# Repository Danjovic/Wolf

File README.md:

# Wolf - Warning: Beta
Atari Jaguar/SNES controller adapter for emulate a Joystick and a Keypad for systems 2600 and 7800

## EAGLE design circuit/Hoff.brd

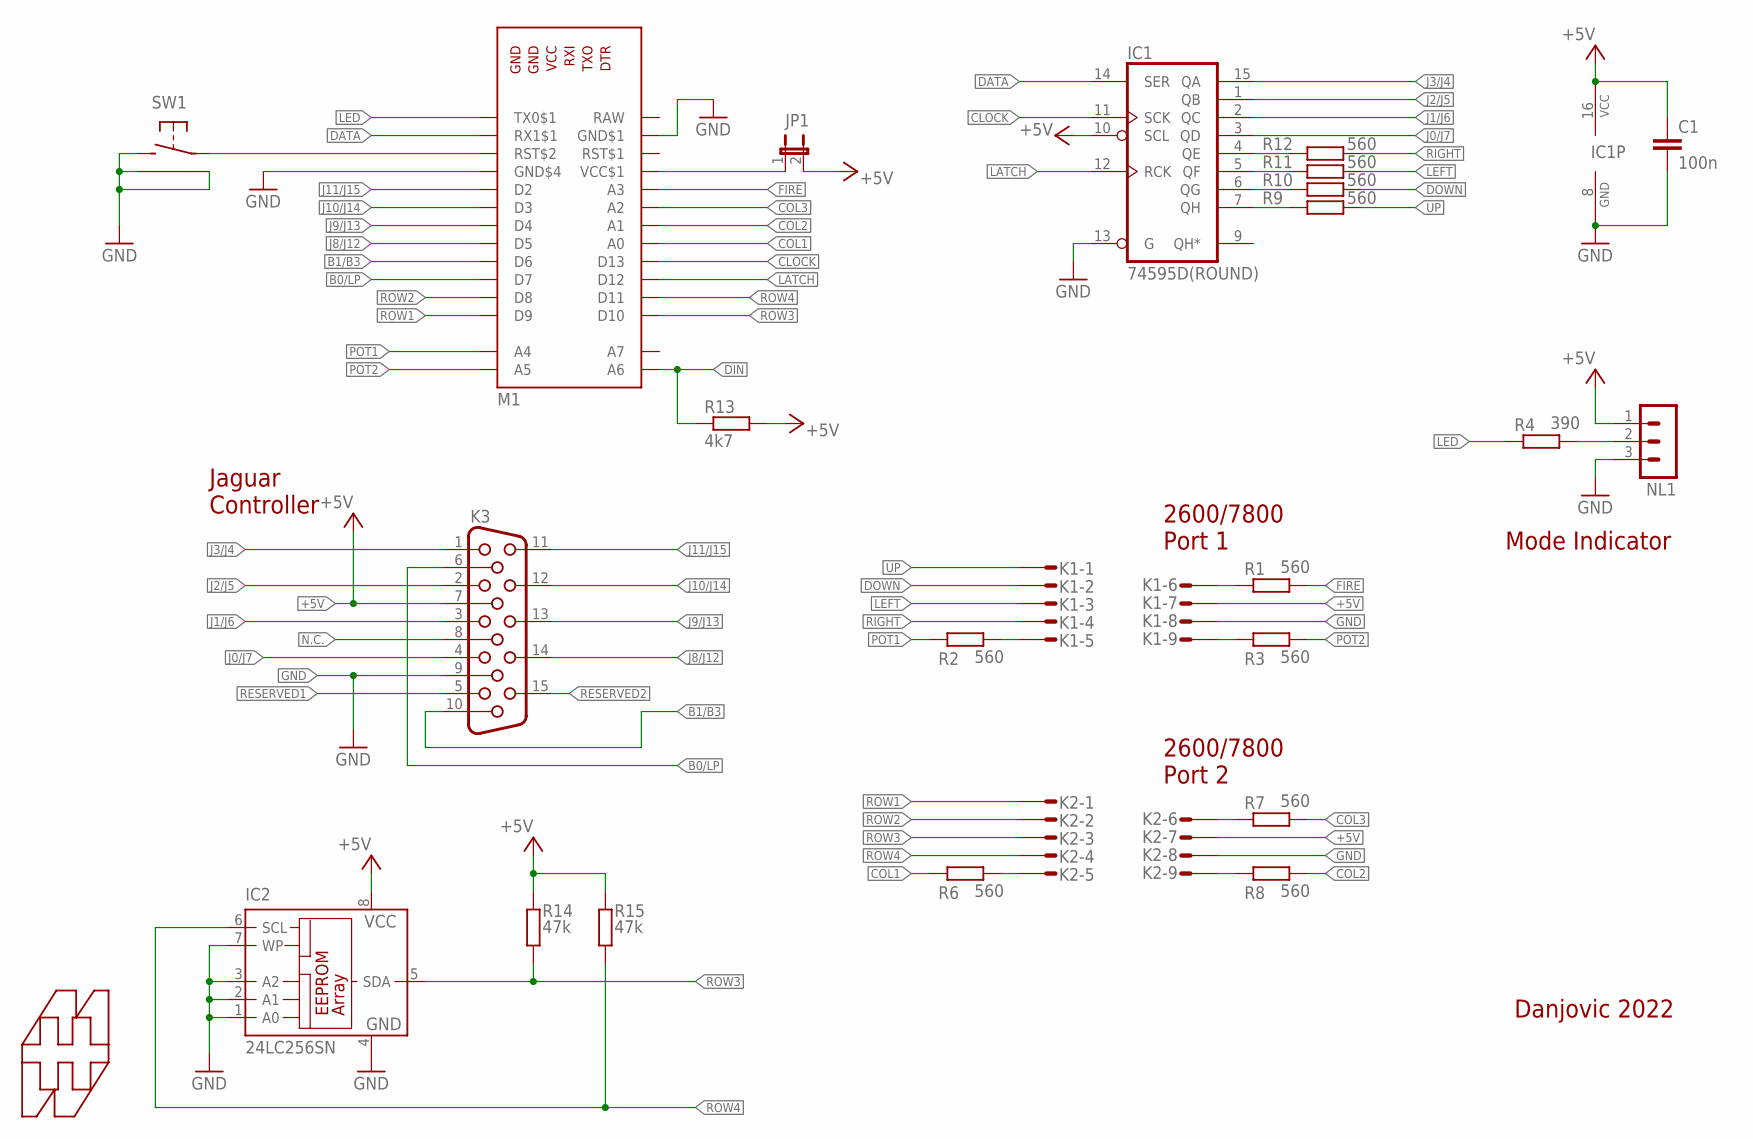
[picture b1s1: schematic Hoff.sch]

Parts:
C1: 100n; C050-024X044
IC1: 74595D(ROUND); DIL16-ROUND
IC2: 24LC256SN; SO-08
JP1: JP1E; JP1
K1, K2: S09P
K3: HF15H; HDF15H
M1: ARDUINO_PRO_MINI_SIDE_ONLY; ARDUNIO_PRO_MINI_SIDE_ONLY
NL1: MA03-1
R1, R2, R3, R6, R7, R8, R9, R10, R11, R12: 560; 0204/7
R4: 390; 0204/7
R13: 4k7; 0204/7
R14, R15: 47k; 0204/7
SW: 31-XX-GG; B3F-31XX
U$1: HAMMOND-1593J; 1593J

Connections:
!RESET: M1.RST$2, SW.1
+5V: C1.1, IC1.10 (SCL), IC1.16 (VCC), IC2.8 (VCC), JP1.2, K1.7, K2.7, K3.7, NL1.1, R13.2, R14.2, R15.2
B0/LP: K3.6, M1.D7
B1/B3: K3.10, M1.D6
CLOCK: IC1.11 (SCK), M1.D13
COL1: M1.A0, R6.1
COL2: M1.A1, R8.2
COL3: M1.A2, R7.2
DATA: IC1.14 (SER), M1.RX1$1
DIN: M1.A6, R13.1
DOWN: K1.2, R10.2
FIRE: M1.A3, R1.2
GND: C1.2, IC1.8 (GND), IC1.13 (G), IC2.1 (A0), IC2.2 (A1), IC2.3 (A2), IC2.4 (GND), IC2.7 (WP), K1.8, K2.8, K3.9, M1.GDN$1 (GND$1), M1.GND$4, NL1.3, SW.2 (S), SW.3, SW.4
J0/J7: IC1.3 (QD), K3.4
J1/J6: IC1.2 (QC), K3.3
J2/J5: IC1.1 (QB), K3.2
J3/J4: IC1.15 (QA), K3.1
J8/J12: K3.14, M1.D5
J9/J13: K3.13, M1.D4
J10/J14: K3.12, M1.D3
J11/J15: K3.11, M1.D2
LATCH: IC1.12 (RCK), M1.D12
LED: M1.TX0$1, R4.1
LEFT: K1.3, R11.2
unnamed: NL1.2, R4.2
unnamed: JP1.1, M1.VCC$1
N.C.: K3.8
POT1: M1.A4, R2.1
POT2: M1.A5, R3.2
RAW: M1.RAW
RESERVED1: K3.5
RESERVED2: K3.15
RIGHT: K1.4, R12.2
ROW1: K2.1, M1.D9
ROW2: K2.2, M1.D8
ROW3: IC2.5 (SDA), K2.3, M1.D10, R14.1
ROW4: IC2.6 (SCL), K2.4, M1.D11, R15.1
R_COL1: K2.5, R6.2
R_COL2: K2.9, R8.1
R_COL3: K2.6, R7.1
R_DOWN: IC1.6 (QG), R10.1
R_FIRE: K1.6, R1.1
R_LEFT: IC1.5 (QF), R11.1
R_POT1: K1.5, R2.2
R_POT2: K1.9, R3.1
R_RIGHT: IC1.4 (QE), R12.1
R_UP: IC1.7 (QH), R9.1
UP: K1.1, R9.2

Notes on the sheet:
Danjovic 2022
Jaguar Controller
2600/7800 Port 1
2600/7800 Port 2
Mode Indicator

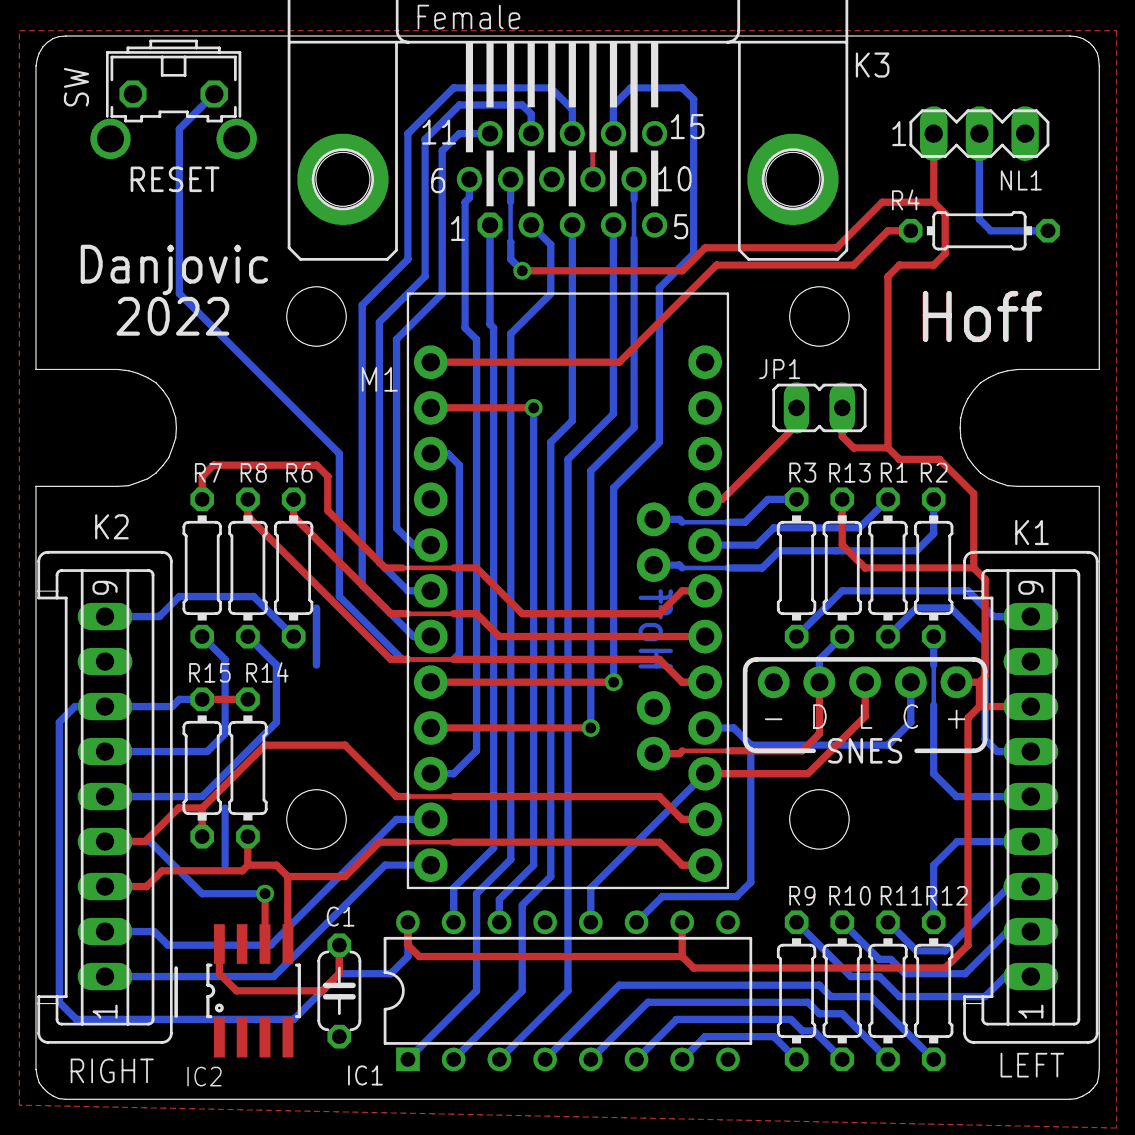
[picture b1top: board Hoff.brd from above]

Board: 2 copper layers, 59.1 x 59.1 mm, 25 parts (0 on the bottom side), 44 nets.

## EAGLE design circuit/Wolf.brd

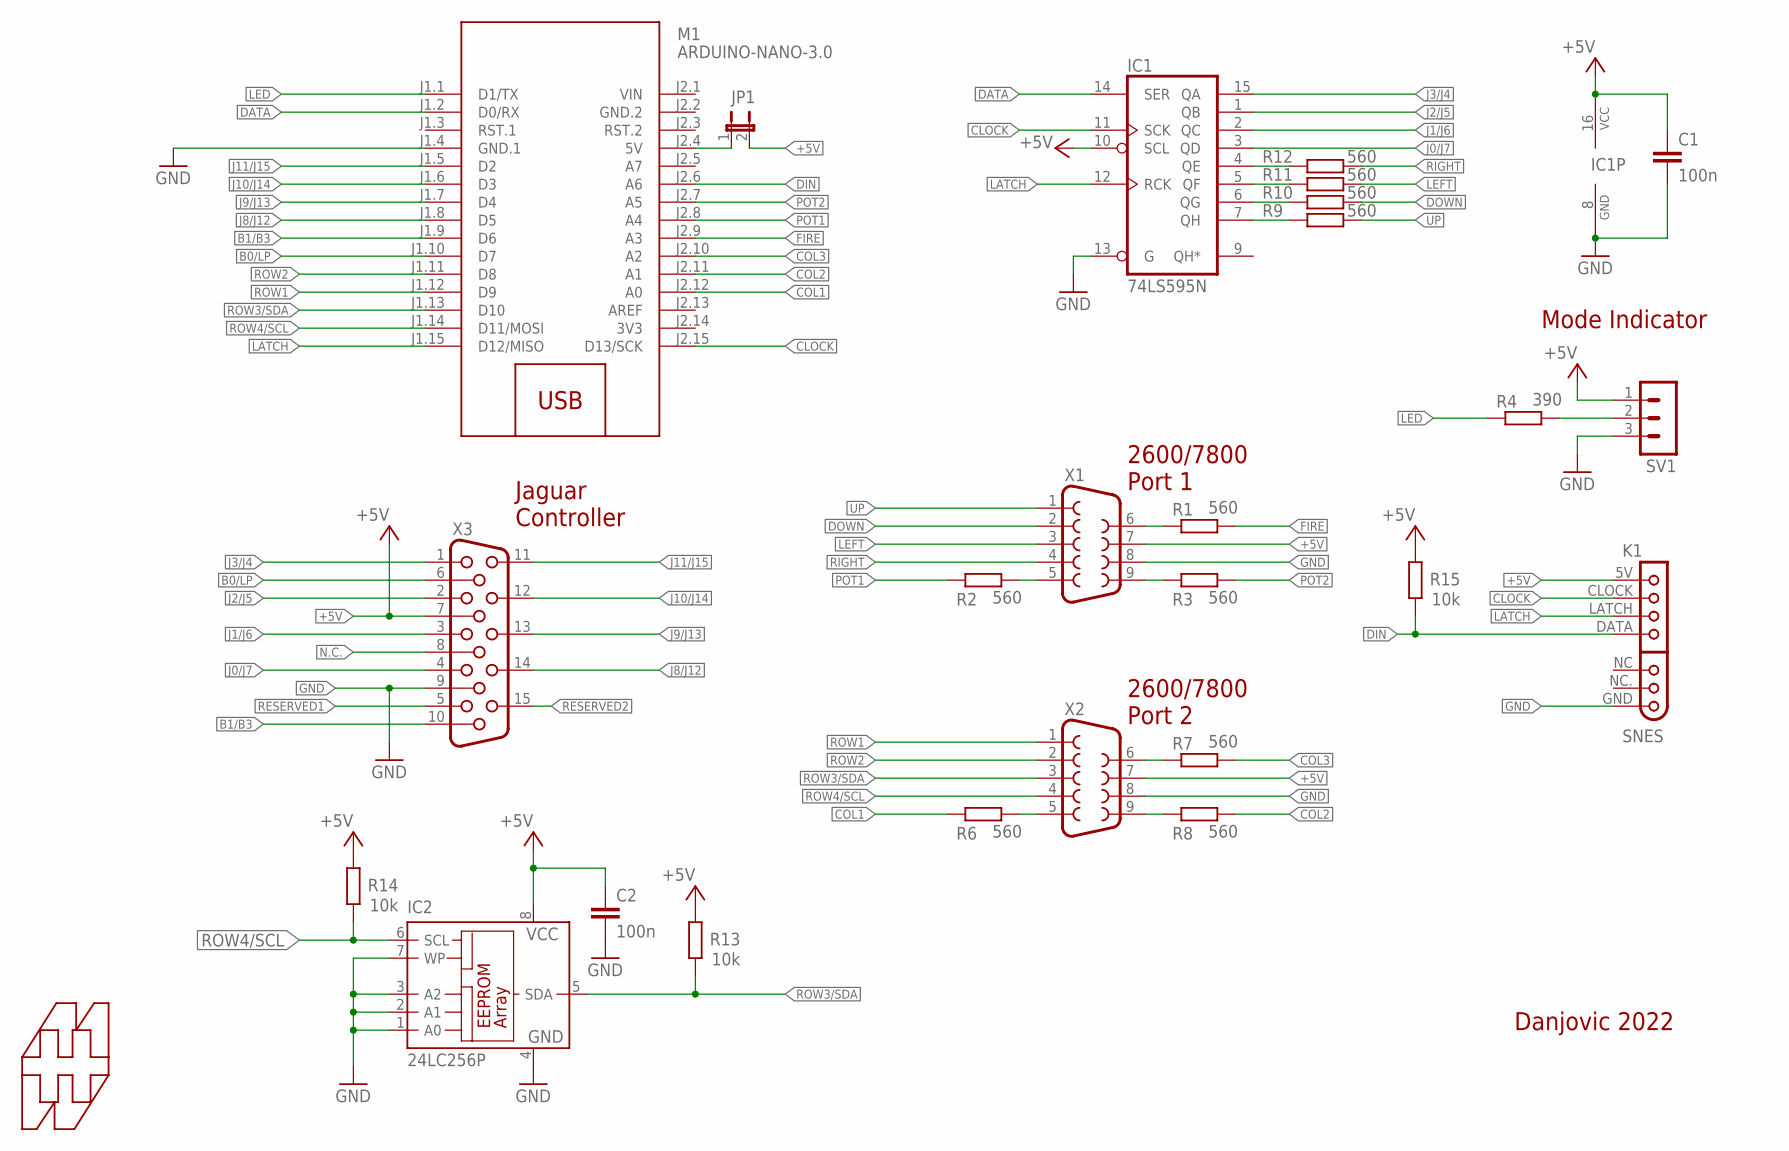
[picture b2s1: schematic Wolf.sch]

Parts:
C1, C2: 100n; C050-024X044
IC1: 74LS595N; DIL16
IC2: 24LC256P; DIL8
JP1: JP1E; JP1
K1: SNES; SNESCON-R
M1: ARDUINO-NANO-3.0
R1, R2, R3, R6, R7, R8, R9, R10, R11, R12: 560; 0204/7
R4: 390; 0204/7
R13, R14, R15: 10k; 0204/7
SV1: MA03-1
U$1: HAMMOND-RL6015; RL6015
X1, X2: F09HP
X3: HF15H; HDF15H

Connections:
3V3: M1.J2.14 (3V3)
+5V: C1.1, C2.1, IC1.10 (SCL), IC1.16 (VCC), IC2.8 (VCC), JP1.2, K1.5V (1), R13.2, R14.2, R15.2, SV1.1, X1.7, X2.7, X3.7
B0/LP: M1.J1.10 (D7), X3.6
B1/B3: M1.J1.9 (D6), X3.10
CLOCK: IC1.11 (SCK), K1.CLOCK (2), M1.J2.15 (D13/SCK)
COL1: M1.J2.12 (A0), R6.1
COL2: M1.J2.11 (A1), R8.2
COL3: M1.J2.10 (A2), R7.2
DATA: IC1.14 (SER), M1.J1.2 (D0/RX)
DIN: K1.DATA (4), M1.J2.6 (A6), R15.1
DOWN: R10.2, X1.2
FIRE: M1.J2.9 (A3), R1.2
GND: C1.2, C2.2, IC1.8 (GND), IC1.13 (G), IC2.1 (A0), IC2.2 (A1), IC2.3 (A2), IC2.4 (GND), IC2.7 (WP), K1.GND (7), M1.J1.4 (GND.1), SV1.3, X1.8, X2.8, X3.9
GND.2: M1.J2.2 (GND.2)
J0/J7: IC1.3 (QD), X3.4
J1/J6: IC1.2 (QC), X3.3
J2/J5: IC1.1 (QB), X3.2
J3/J4: IC1.15 (QA), X3.1
J8/J12: M1.J1.8 (D5), X3.14
J9/J13: M1.J1.7 (D4), X3.13
J10/J14: M1.J1.6 (D3), X3.12
J11/J15: M1.J1.5 (D2), X3.11
LATCH: IC1.12 (RCK), K1.LATCH (3), M1.J1.15 (D12/MISO)
LED: M1.J1.1 (D1/TX), R4.1
LEFT: R11.2, X1.3
unnamed: R4.2, SV1.2
N.C.: X3.8
POT1: M1.J2.8 (A4), R2.1
POT2: M1.J2.7 (A5), R3.2
RESERVED1: X3.5
RESERVED2: X3.15
RIGHT: R12.2, X1.4
ROW1: M1.J1.12 (D9), X2.1
ROW2: M1.J1.11 (D8), X2.2
ROW3/SDA: IC2.5 (SDA), M1.J1.13 (D10), R13.1, X2.3
ROW4/SCL: IC2.6 (SCL), M1.J1.14 (D11/MOSI), R14.1, X2.4
R_COL1: R6.2, X2.5
R_COL2: R8.1, X2.9
R_COL3: R7.1, X2.6
R_DOWN: IC1.6 (QG), R10.1
R_FIRE: R1.1, X1.6
R_LEFT: IC1.5 (QF), R11.1
R_POT1: R2.2, X1.5
R_POT2: R3.1, X1.9
R_RIGHT: IC1.4 (QE), R12.1
R_UP: IC1.7 (QH), R9.1
UP: R9.2, X1.1
VCC_ARD: JP1.1, M1.J2.4 (5V)
VIN: M1.J2.1 (VIN)

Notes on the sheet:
Danjovic 2022
Jaguar Controller
2600/7800 Port 1
2600/7800 Port 2
Mode Indicator

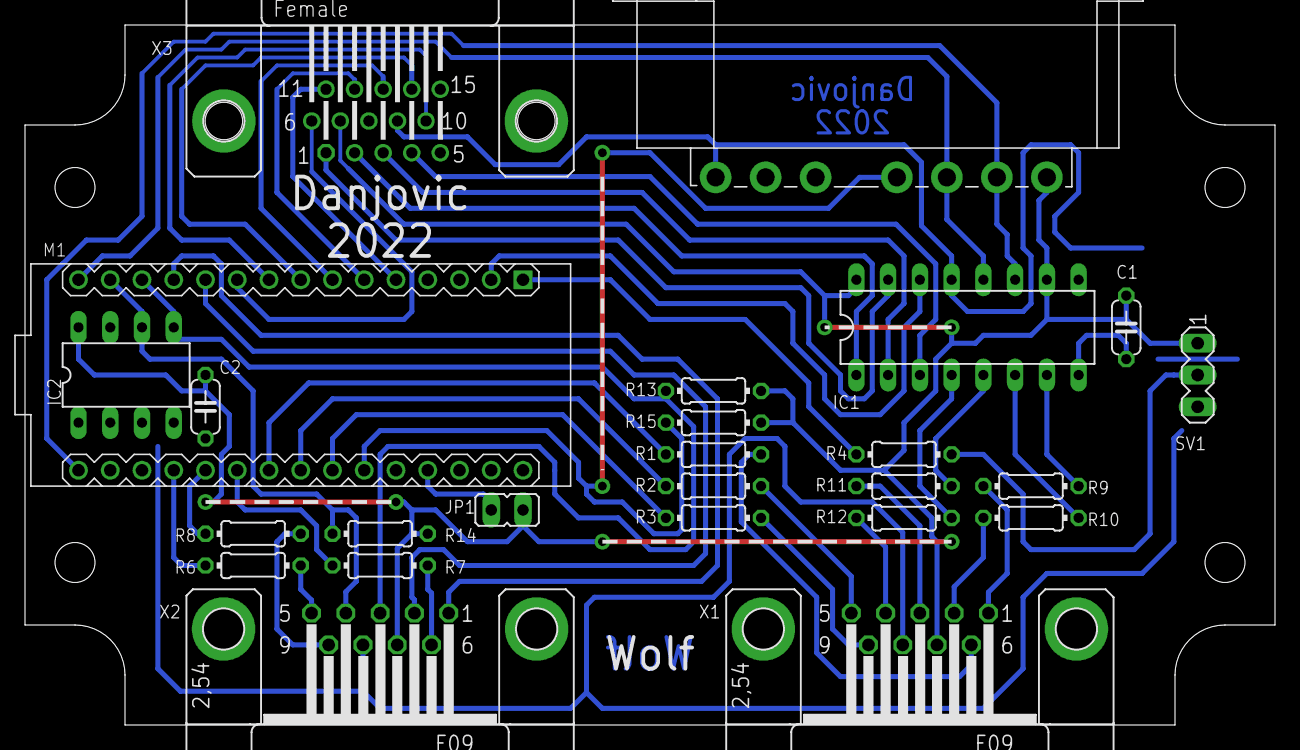
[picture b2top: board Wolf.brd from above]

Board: 2 copper layers, 100.0 x 56.0 mm, 26 parts (0 on the bottom side), 43 nets.

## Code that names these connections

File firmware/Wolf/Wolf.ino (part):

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
#define _DATA        0
#define _LED         1
#define LATCH       12
#define CLOCK       13
#define _SNES_DIN   A6

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//   | '  \/ _` / _| '_/ _ (_-<
//   |_|_|_\__,_\__|_| \___/__/
//
#define latchLow()   digitalWrite(LATCH,LOW)
#define latchHigh()  digitalWrite(LATCH,HIGH)
#define clockHigh()  digitalWrite(CLOCK,HIGH)
#define clockLow()   digitalWrite(CLOCK,LOW)
#define dataLow()    digitalWrite(_DATA,LOW)
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#endif

  pinMode(_DATA, OUTPUT);                        // TODO: incorporate definition in instructions above
  pinMode(LATCH, OUTPUT);
  pinMode(CLOCK, OUTPUT);
  pinMode(_SNES_DIN, INPUT);

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  uint8_t colSelected = PIN_KEYPAD_ROWS_IN;
  uint8_t colData;

  switch (colSelected & 0x0f) {  // pins row2/row1 swapped

    case 0b00001101:            // COL 1   7   6   5   4   3   2   1   0
      colData = atariKeypad[0]; //        Hi  Hi  Hi  Hi  Hi   3   2   1
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
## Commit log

2022-01-15 Update LICENSE
2022-01-16 added contention protect resistors
2022-01-16 updated indexes on sampleAndProcessControllerData() function
2022-01-17 updated pcb
2022-01-17 updated iimages
2022-01-17 added macros on button association logic
2022-02-26 Assed savekey eeprom to the circuit
2022-03-20 Added missing connection to GND
2022-03-20 Added missing GND connection
2022-03-20 Some debug performed, still WIP
2022-03-20 Changed resistor for bicolor LED
2022-03-20 updated pictures
2022-03-20 remove obsolete file
2022-03-23 Just uploading, still wip
2022-03-28 SNES controller working.
2022-03-28 Shortened PCB
2022-04-09 Beta
    Working with either Jaguar or SNES controller. Not working with both at the same time by now
2022-04-09 (Beta) Exclusive operation of SNES / Jaguar controller
2022-04-12 Added neopixel to indicate operating mode

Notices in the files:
firmware/Wolf/Wolf.ino:
Danjovic 2022 - Released under Creative Commons Zero v1.0 Universal
parts and their libraries:
diy-modules: Released under the Creative Commons Attribution 4.0 International License: http://creativecommons.org/licenses/by/4.0
